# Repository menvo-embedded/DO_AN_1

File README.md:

# Warehouse Access RFID + Computer Vision

Graduation project prototype for warehouse access control and employee
monitoring using ESP32 RFID, cameras, YOLO detection, tracking, Re-ID,
optional face recognition, fusion logic, SQLite, and a Flask dashboard.

## Main Components

- `firmware/`: ESP32 Arduino firmware for RC522 RFID, LCD I2C, buzzer, servo
  gate, WiFi, NTP, and MQTT event publishing.
- `python_cv/`: main PC-side application for camera processing, Re-ID,
  InsightFace hybrid recognition, RFID/CV fusion, SQLite storage, and dashboard.
- `hardware/`: KiCad PCB source files, custom footprints, 3D models, and Gerber
  export for the RFID controller board.
- `docs/`: submission notes, demo guide, diagrams, and report assets.
- `experiments/`, `python_cv/tools/`, `python_cv/tests/`: debug, calibration,
  data collection, and validation utilities.

The active PC pipeline is `python_cv/main.py`. The nested folder
`warehouse-access-rfid-cv/` is an older/stale copy and should not be used for
the final submission without review.

## Setup

```powershell
python -m venv .venv
.\.venv\Scripts\Activate.ps1
python -m pip install --upgrade pip
pip install -r requirements.txt
```

If CUDA-specific PyTorch wheels are required, install PyTorch first using the
official command for the target GPU/CUDA version, then install the remaining
requirements.

Copy the clean runtime example and edit local values:

```powershell
Copy-Item .env.example python_cv\.env
```

Do not commit `python_cv/.env`, RTSP passwords, WiFi passwords, raw videos,
face/person galleries, or private datasets.

## Dataset and Local Data Path

AI datasets, raw videos, review crops, galleries, and model artifacts are local
runtime assets. They are intentionally not part of the source-code submission.

Default local dataset root:

```text
D:\warehouse_dataset
```

Default subfolders used by tools:

```text
D:\warehouse_dataset\dataset_crops
D:\warehouse_dataset\raw_videos_full
D:\warehouse_dataset\review_crops_reid_yoloseg
D:\warehouse_dataset\raw_videos_from_imou_sd
```

These defaults are configured through `.env`:

```text
WAREHOUSE_DATASET_ROOT=D:/warehouse_dataset
DATASET_CROPS_ROOT=D:/warehouse_dataset/dataset_crops
RAW_VIDEO_ROOT=D:/warehouse_dataset/raw_videos_full
REVIEW_CROP_ROOT=D:/warehouse_dataset/review_crops_reid_yoloseg
IMOU_SD_VIDEO_ROOT=D:/warehouse_dataset/raw_videos_from_imou_sd
```

If another machine uses a different drive or folder, edit `python_cv/.env`
instead of changing code. To copy local data from the old external `F:` drive to
`D:`, review and run:

```powershell
.\scripts\migrate_warehouse_dataset_F_to_D.ps1
.\scripts\verify_dataset_paths.ps1
```

The migration script copies data only; it does not delete anything from `F:`.

## Run Demo

From the repository root:

```powershell
cd python_cv
python main.py
```

Default demo mode can run CV-only with Zone 2 webcam and InsightFace enabled.
For RFID + CV end-to-end, set `ENABLE_MQTT=true`, configure the MQTT broker,
flash the ESP32 firmware, and start the broker before running `python main.py`.
Create `firmware/config/device_config.h` from
`firmware/config/device_config.example.h` before flashing the ESP32.

Dashboard:

```text
http://localhost:5000
```

Detailed demo steps are in `docs/RUN_DEMO.md`.

## Submission Notes

Before submitting, review:

- `CLEANUP_AUDIT_REPORT.md`
- `SUBMISSION_STRUCTURE_PROPOSAL.md`
- `docs/CLEAN_SOURCE_CHECKLIST.md`
- `CLEANUP_COMMANDS_DRAFT.ps1`

The current repo contains local debug outputs, model files, gallery pickles, raw
videos, and real credentials in firmware. Clean or archive them before handing
the project to a reviewer.

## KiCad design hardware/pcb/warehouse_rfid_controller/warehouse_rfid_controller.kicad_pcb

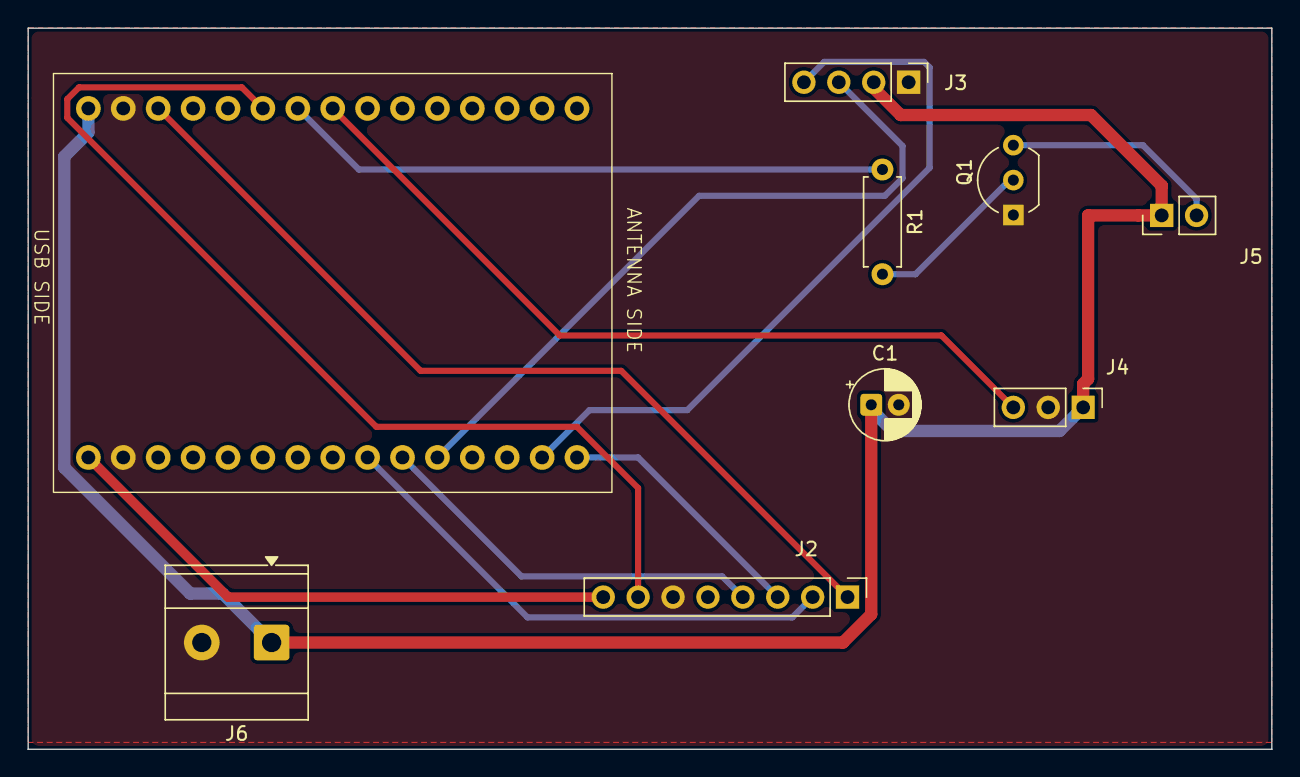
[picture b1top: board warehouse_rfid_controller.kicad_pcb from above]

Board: 2 copper layers, 90.5 x 52.5 mm, 9 parts (0 on the bottom side), 14 nets.

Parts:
C1: 470uF; CP_Radial_D5.0mm_P2.00mm
J2: RC522_RFID; PinHeader_1x08_P2.54mm_Vertical
J3: LCD_I2C; PinHeader_1x04_P2.54mm_Vertical
J4: SERVO_SG90; PinHeader_1x03_P2.54mm_Vertical
J5: BUZZER_2PIN; PinHeader_1x02_P2.54mm_Vertical
J6: POWER_5V_IN; TerminalBlock_MetzConnect_Type073_RT02602HBLU_1x02_P5.08mm_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
Q1: S8050; TO-92_Inline_Wide
R1: 1k; R_Axial_DIN0207_L6.3mm_D2.5mm_P7.62mm_Horizontal
U1: ESP32_DEVKIT_30PIN; ESP32_DEVKIT_V1_DOIT_30PIN

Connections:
/3V3: J2.8, U1.30
/5V: C1.1, J3.2, J4.1, J5.1, J6.1, U1.29
/BUZZER_BASE: Q1.2 (B), R1.2
/BUZZER_NEG: J5.2, Q1.3 (C)
/BUZZER_SIG: R1.1, U1.17
/GND: C1.2, J2.6, J3.1, J4.2, J6.2, Q1.1 (E), U1.27, U1.28
/I2C_SCL: J3.4, U1.4
/I2C_SDA: J3.3, U1.10
/RFID_MISO: J2.4, U1.12
/RFID_MOSI: J2.3, U1.2
/RFID_RST: J2.7, U1.19
/RFID_SCK: J2.2, U1.14
/RFID_SS: J2.1, U1.25
/SERVO_SIG: J4.3, U1.15

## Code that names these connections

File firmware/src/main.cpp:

#include <Arduino.h>
#include <Wire.h>
#include <SPI.h>
#include <MFRC522.h>
#include <LiquidCrystal_I2C.h>
#include <ESP32Servo.h>
#include <WiFi.h>
#include <PubSubClient.h>
#include <time.h>

#if __has_include("../config/device_config.h")
#include "../config/device_config.h"
#else
#define DEVICE_WIFI_SSID "YOUR_WIFI"
#define DEVICE_WIFI_PASSWORD "YOUR_PASSWORD"
#define DEVICE_MQTT_BROKER "192.168.88.229"
#define DEVICE_MQTT_PORT 1883
#define DEVICE_MQTT_TOPIC "warehouse/rfid/scan"
#define DEVICE_MQTT_CLIENT "esp32-door-01"
#define DEVICE_NTP_SERVER "pool.ntp.org"
#define DEVICE_GMT_OFFSET 25200
#define DEVICE_DAYLIGHT_OFFSET 0
#endif

#define RFID_SS_PIN    13
#define RFID_SCK_PIN   18 
#define RFID_MOSI_PIN  23
#define RFID_MISO_PIN  19
#define RFID_RST_PIN   27

#define LCD_SDA_PIN    21
#define LCD_SCL_PIN    22

#define BUZZER_PIN     26
#define SERVO_PIN      25

// LED trạng thái
#define LED_GREEN_PIN  32   // LED xanh: thẻ hợp lệ / mở cổng
#define LED_RED_PIN    33   // LED đỏ: thẻ không hợp lệ / từ chối

#define GATE_CLOSE_ANGLE 0
#define GATE_OPEN_ANGLE  90

const char* WIFI_SSID   = DEVICE_WIFI_SSID;
const char* WIFI_PASS   = DEVICE_WIFI_PASSWORD;

const char* MQTT_BROKER = DEVICE_MQTT_BROKER;
const int   MQTT_PORT   = DEVICE_MQTT_PORT;
const char* MQTT_TOPIC  = DEVICE_MQTT_TOPIC;
const char* MQTT_CLIENT = DEVICE_MQTT_CLIENT;
const char* NTP_SERVER  = DEVICE_NTP_SERVER;
const long  GMT_OFFSET  = DEVICE_GMT_OFFSET;
const int   DAYLIGHT_OFF = DEVICE_DAYLIGHT_OFFSET;

struct Card { 
  const char* empId; 
  byte uid[4]; 
};

Card allowedCards[] = {
  {"NV001", {0x03, 0xF7, 0x63, 0x28}},
  {"NV002", {0x23, 0xFC, 0xDA, 0x26}},
  {"NV003", {0xF3, 0xAC, 0x71, 0x28}},
  {"NV004", {0x43, 0x8D, 0xFE, 0x27}},
  {"NV005", {0x95, 0xB0, 0xF6, 0x05}},
};

const int CARD_COUNT = sizeof(allowedCards) / sizeof(allowedCards[0]);

LiquidCrystal_I2C lcd(0x27, 16, 2);
MFRC522 rfid(RFID_SS_PIN, RFID_RST_PIN);
Servo gateServo;

WiFiClient wifiClient;
PubSubClient mqtt(wifiClient);

unsigned long lastScanTime = 0;
const unsigned long scanCooldown = 1500;

unsigned long gateOpenTime = 0;
bool gateIsOpen = false;

void lcdShow(const char* line1, const char* line2 = "") {
  lcd.clear();
  lcd.setCursor(0, 0); 
  lcd.print(line1);

  lcd.setCursor(0, 1); 
  lcd.print(line2);
}

// ===================== LED =====================
void ledOff() {
  digitalWrite(LED_GREEN_PIN, LOW);
  digitalWrite(LED_RED_PIN, LOW);
}

void ledSuccess() {
  digitalWrite(LED_GREEN_PIN, HIGH);
  digitalWrite(LED_RED_PIN, LOW);
}

void ledFail() {
  digitalWrite(LED_GREEN_PIN, LOW);
  digitalWrite(LED_RED_PIN, HIGH);
}

// ===================== BUZZER =====================
void beep(int ms) {
  digitalWrite(BUZZER_PIN, HIGH); 
  delay(ms); 
  digitalWrite(BUZZER_PIN, LOW);
}

void beepSuccess() { 
  beep(50); 
  delay(80); 
  beep(50); 
}

void beepFail() { 
  beep(200); 
}

// ===================== SERVO =====================
void openGate() {
  gateServo.write(GATE_OPEN_ANGLE);
  gateOpenTime = millis();
  gateIsOpen = true;
}

// ===================== TIME =====================
String getTimestamp() {
  struct tm t;

  // Timeout 0ms: trả về ngay, không block chờ NTP sync.
  // Nếu NTP chưa sync thì dùng fallback epoch.
  if (!getLocalTime(&t, 0)) {
    return "1970-01-01T00:00:00+07:00";
  }

  char buf[30];
  strftime(buf, sizeof(buf), "%Y-%m-%dT%H:%M:%S+07:00", &t);
  return String(buf);
}

// ===================== RFID =====================
String getUIDString(MFRC522::Uid* uid) {
  String s = "";

  for (byte i = 0; i < uid->size; i++) {
    if (uid->uidByte[i] < 0x10) s += "0";
    s += String(uid->uidByte[i], HEX);
  }

  s.toUpperCase();
  return s;
}

const char* findEmployee(MFRC522::Uid* uid) {
  if (uid->size != 4) return NULL;

  for (int i = 0; i < CARD_COUNT; i++) {
    bool match = true;

    for (byte j = 0; j < 4; j++) {
      if (uid->uidByte[j] != allowedCards[i].uid[j]) { 
        match = false; 
        break; 
      }
    }

    if (match) return allowedCards[i].empId;
  }

  return NULL;
}

// ===================== MQTT =====================
void publishMQTT(const char* empId, const String& uid, const String& ts) {
  if (WiFi.status() != WL_CONNECTED) {
    Serial.println("[MQTT] Skip: WiFi not connected");
    return;
  }

  // Không reconnect blocking tại đây — loop() đã xử lý reconnect non-blocking.
  // Nếu chưa connected thì bỏ qua lần publish này, tránh delay buzzer/servo.
  if (!mqtt.connected()) {
    Serial.println("[MQTT] Skip: not connected (reconnect handled in loop)");
    return;
  }

  String payload = "{\"uid\":\"" + uid + "\","
                   "\"employee_id\":\"" + String(empId) + "\","
                   "\"timestamp\":\"" + ts + "\","
                   "\"device\":\"door-01\","
                   "\"zone\":1}";

  bool ok = mqtt.publish(MQTT_TOPIC, payload.c_str());
  Serial.println(ok ? "[MQTT] Published OK" : "[MQTT] Publish FAIL");
}

void setup() {
  Serial.begin(115200);
  delay(1000);

  pinMode(BUZZER_PIN, OUTPUT);
  digitalWrite(BUZZER_PIN, LOW);

  // LED setup
  pinMode(LED_GREEN_PIN, OUTPUT);
  pinMode(LED_RED_PIN, OUTPUT);
  ledOff();

  gateServo.setPeriodHertz(50);
  gateServo.attach(SERVO_PIN, 500, 2400);
  gateServo.write(GATE_CLOSE_ANGLE);

  Wire.begin(LCD_SDA_PIN, LCD_SCL_PIN);
  lcd.init();
  lcd.backlight();
  lcdShow("He thong kho", "Khoi dong...");
  delay(800);

  SPI.begin(RFID_SCK_PIN, RFID_MISO_PIN, RFID_MOSI_PIN, RFID_SS_PIN);
  rfid.PCD_Init();

  byte v = rfid.PCD_ReadRegister(MFRC522::VersionReg);
  Serial.print("VersionReg = 0x"); 
  Serial.println(v, HEX);

  if (v == 0x00 || v == 0xFF) {
    lcdShow("Loi RC522", "Kiem tra day");

    while (true) { 
      ledFail();
      beep(100); 
      delay(1000); 
      ledOff();
      delay(300);
    }
  }

  WiFi.begin(WIFI_SSID, WIFI_PASS);
  mqtt.setServer(MQTT_BROKER, MQTT_PORT);
  configTime(GMT_OFFSET, DAYLIGHT_OFF, NTP_SERVER);

  lcdShow("Moi quet the", "");

  // Báo hệ thống khởi động OK
  ledSuccess();
  beep(60);
  delay(300);
  ledOff();
}

void loop() {
  // Đóng gate sau 3s non-blocking
  if (gateIsOpen && millis() - gateOpenTime >= 3000) {
    gateServo.write(GATE_CLOSE_ANGLE);
    gateIsOpen = false;

    // Tắt LED xanh khi cổng đóng
    ledOff();
  }

  // MQTT/WiFi xử lý phụ, không được chặn RFID
  if (WiFi.status() == WL_CONNECTED) {
    if (!mqtt.connected()) mqtt.connect(MQTT_CLIENT);
    mqtt.loop();
  }

  // Cooldown
  if (millis() - lastScanTime < scanCooldown) { 
    delay(20); 
    return; 
  }

  if (!rfid.PICC_IsNewCardPresent()) { 
    delay(20); 
    return; 
  }

  if (!rfid.PICC_ReadCardSerial()) { 
    delay(20); 
    return; 
  }

  unsigned long t_detect = millis();
  String uid = getUIDString(&rfid.uid);
  // getTimestamp() không gọi ở đây — tránh getLocalTime() block 5s khi NTP chưa sync.
  // Timestamp sẽ lấy sau physical feedback, chỉ cần trước publishMQTT.

  Serial.printf("[T=%lu] CARD DETECTED uid=%s\n", t_detect, uid.c_str());

  const char* empId = findEmployee(&rfid.uid);

  if (empId != NULL) {
    Serial.printf("[T=%lu] CARD VALID emp=%s\n", millis(), empId);

    // Phản hồi vật lý TRƯỚC — không gọi NTP/WiFi/MQTT trước bước này
    ledSuccess();
    lcdShow(empId, "Mo cong...");
    beepSuccess();
    openGate();
    Serial.printf("[T=%lu] PHYSICAL FEEDBACK NOW\n", millis());

    // Lấy timestamp SAU physical feedback rồi mới publish MQTT
    String ts = getTimestamp();
    Serial.printf("[T=%lu] BEFORE MQTT\n", millis());
    publishMQTT(empId, uid, ts);
    Serial.printf("[T=%lu] AFTER MQTT\n", millis());

  } else {
    Serial.printf("[T=%lu] CARD INVALID uid=%s\n", millis(), uid.c_str());

    ledFail();
    lcdShow("Khong hop le", "Bi tu choi");
    beepFail();

    delay(1000);
    ledOff();
  }

  Serial.println("------------------------");

  lastScanTime = millis();

  rfid.PICC_HaltA();
  rfid.PCD_StopCrypto1();

  delay(500);
  lcdShow("Moi quet the", "");
}
